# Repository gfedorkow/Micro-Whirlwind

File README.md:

Schematic and printed circuit KiCad design files for a hand-held Whirlwind emulator based on the Raspberry Pi

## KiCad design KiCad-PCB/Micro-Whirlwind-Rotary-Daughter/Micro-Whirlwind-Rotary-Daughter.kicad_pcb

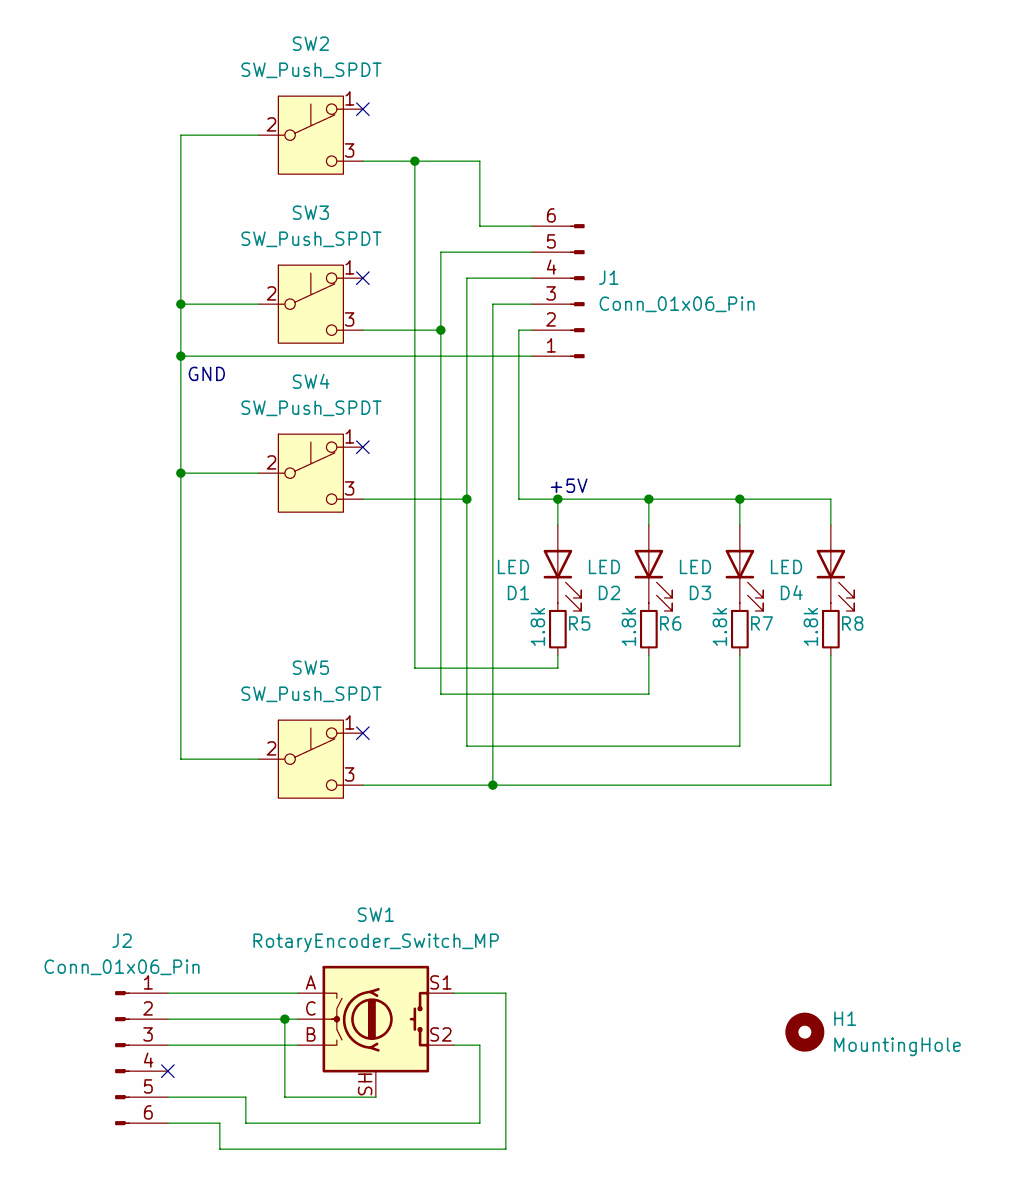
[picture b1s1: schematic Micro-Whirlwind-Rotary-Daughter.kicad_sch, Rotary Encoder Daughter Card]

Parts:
D1, D2, D3, D4: LED; LED_D3.0mm
H1: MountingHole; MountingHole_3.2mm_M3
J1, J2: Conn_01x06_Pin; PinHeader_1x06_P2.54mm_Vertical
R5, R6, R7, R8: 1.8k; R_1206_3216Metric_Pad1.30x1.75mm_HandSolder
SW1: RotaryEncoder_Switch_MP; RotaryEncoder_Bourns_Vertical_PEC12R-3x17F-Sxxxx
SW2, SW3, SW4, SW5: SW_Push_SPDT; PinHeader_1x03_P2.54mm_Vertical

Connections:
unnamed: D1.2 (A), D2.2 (A), D3.2 (A), D4.2 (A), J1.2
unnamed: D1.1 (K), R5.1
unnamed: D2.1 (K), R6.1
unnamed: D3.1 (K), R7.1
unnamed: D4.1 (K), R8.1
unnamed: J1.1, SW2.2 (B), SW3.2 (B), SW4.2 (B), SW5.2 (B)
unnamed: J1.3, R8.2, SW5.3 (C)
unnamed: J1.4, R7.2, SW4.3 (C)
unnamed: J1.5, R6.2, SW3.3 (C)
unnamed: J1.6, R5.2, SW2.3 (C)
unnamed: J2.1, SW1.A
unnamed: J2.2, SW1.C, SW1.SH
unnamed: J2.3, SW1.B
unnamed: J2.5, SW1.S2
unnamed: J2.6, SW1.S1

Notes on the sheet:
GND
+5V

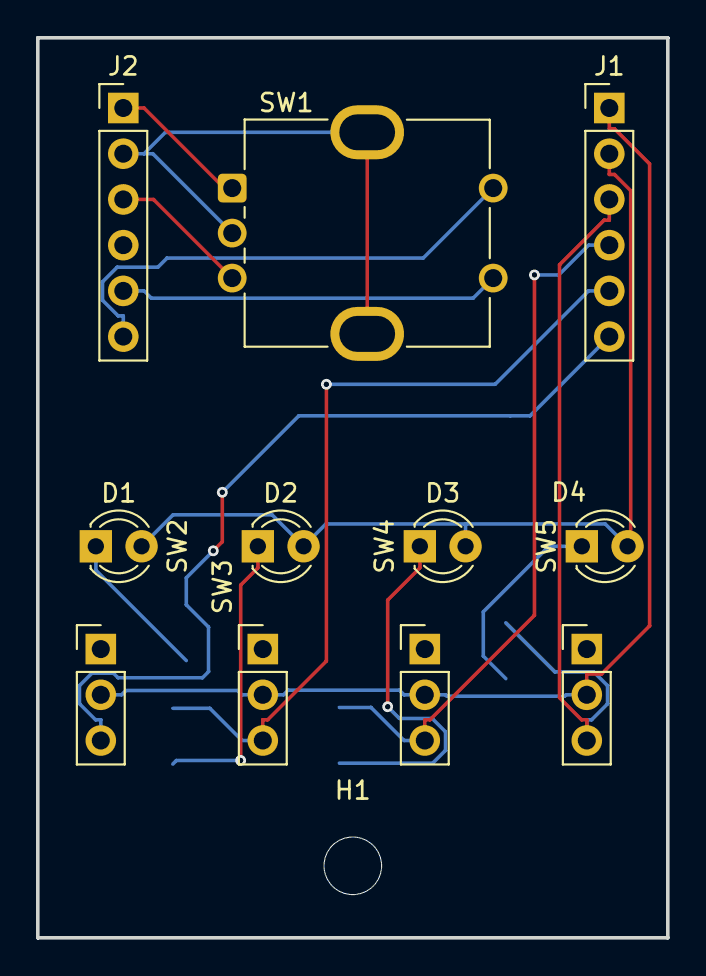
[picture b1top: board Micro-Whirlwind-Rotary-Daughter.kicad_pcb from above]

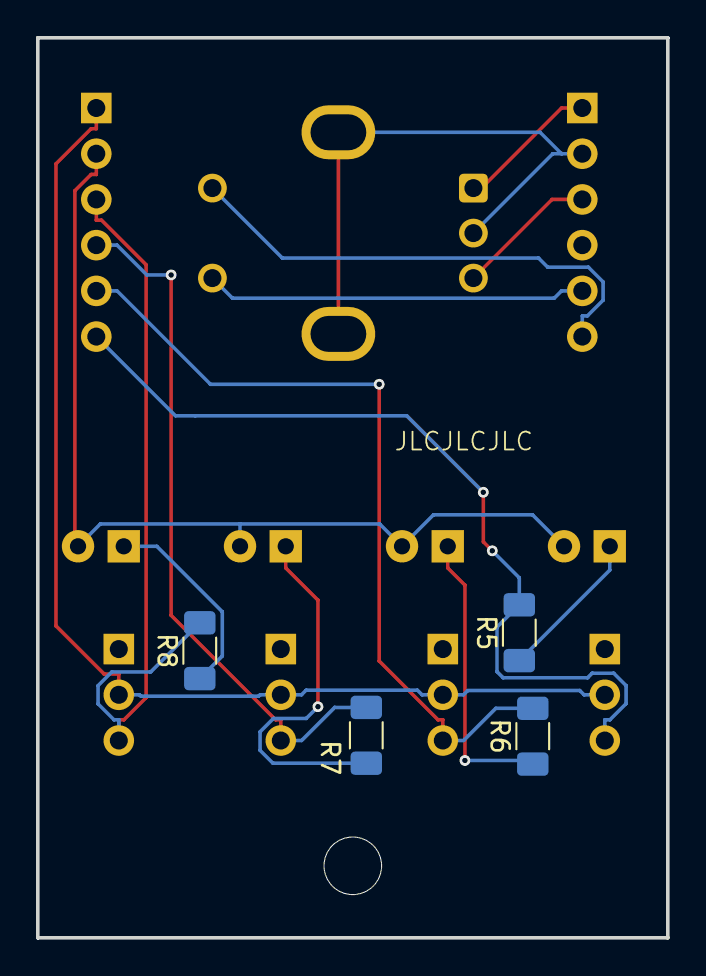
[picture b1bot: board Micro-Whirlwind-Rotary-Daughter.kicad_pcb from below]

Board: 2 copper layers, 35.0 x 50.0 mm, 16 parts (4 on the bottom side), 15 nets.

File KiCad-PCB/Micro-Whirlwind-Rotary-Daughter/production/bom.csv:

Designator,Footprint,Quantity,Value,LCSC Part #
"D1, D2, D3, D4",LED_D3.0mm,4,LED,
"J1, J2",PinHeader_1x06_P2.54mm_Vertical,2,Conn_01x06_Pin,
"R5, R6, R7, R8",1206,4,1.8k,
SW1,RotaryEncoder_Bourns_Vertical_PEC12R-3x17F-Sxxxx,1,RotaryEncoder_Switch_MP,
"SW2, SW3, SW4, SW5",PinHeader_1x03_P2.54mm_Vertical,4,SW_Push_SPDT,

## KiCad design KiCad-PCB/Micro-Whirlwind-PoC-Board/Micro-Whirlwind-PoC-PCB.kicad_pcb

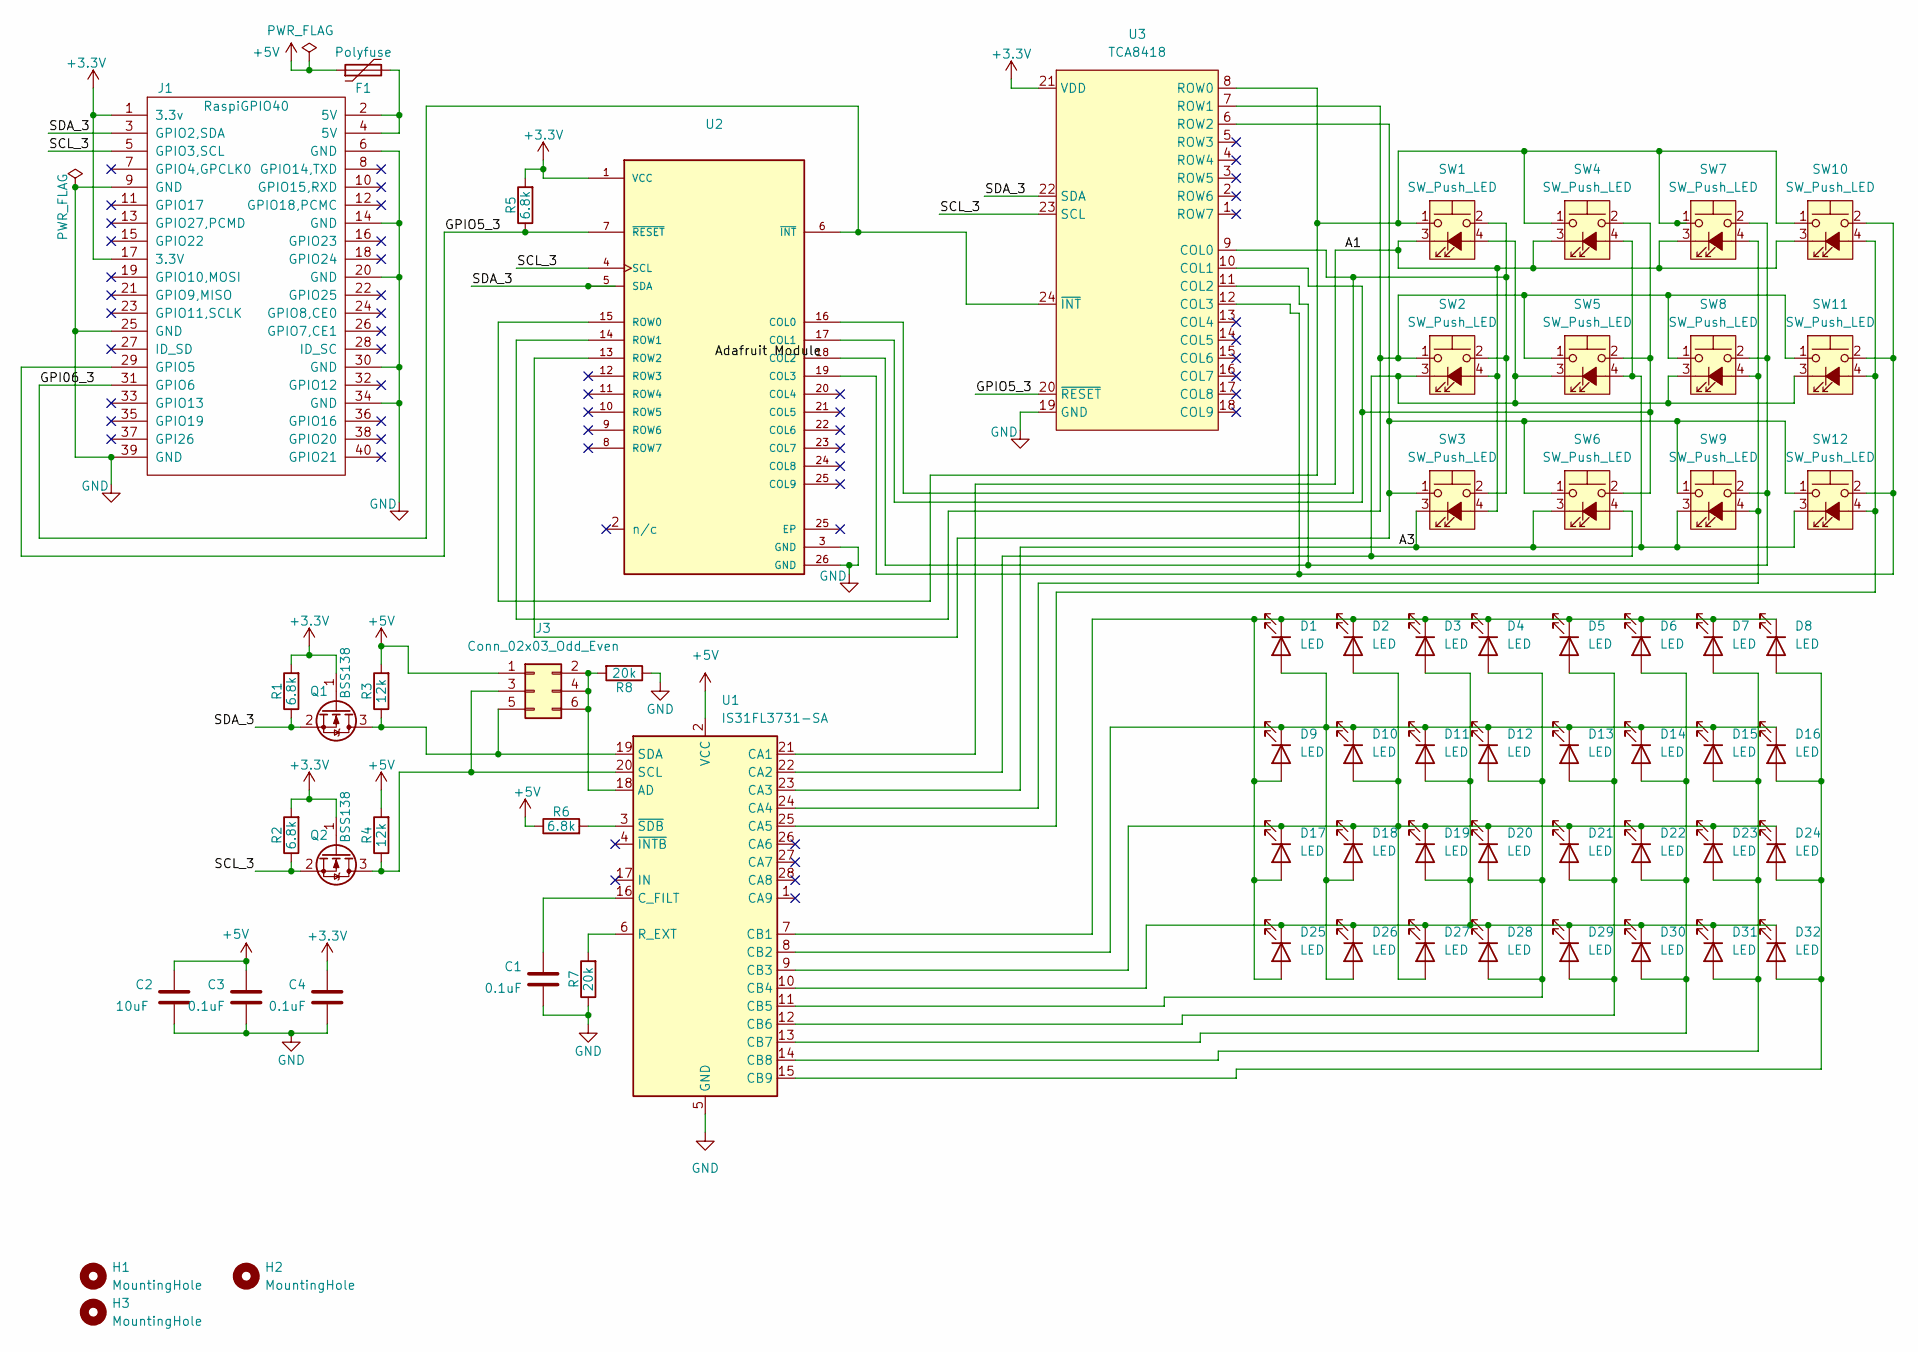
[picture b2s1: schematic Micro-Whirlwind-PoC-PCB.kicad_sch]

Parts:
C1, C3, C4: 0.1uF; C_Rect_L11.0mm_W2.8mm_P10.00mm_MKT
C2: 10uF; CP_Radial_D5.0mm_P2.50mm
D1, D2, D3, D4, D5, D6, D7, D8, D9, D10, D11, D12, D13, D14, D15, D16, D17, D18, D19, D20, D21, D22, D23, D24, D25, D26, D27, D28, D29, D30, D31, D32: LED; LED_D3.0mm
F1: Polyfuse; Fuse_Bourns_MF-RG300
H1, H2, H3: MountingHole; MountingHole_2.5mm_panel_cut
J1: RaspiGPIO40; Wannenstecker_2x20_V
J3: Conn_02x03_Odd_Even; PinHeader_2x03_P2.54mm_Vertical
Q1, Q2: BSS138; SOT-23
R1, R2, R5, R6: 6.8k; SM-1206B
R3, R4: 12k; SM-1206B
R7, R8: 20k; SM-1206B
SW1, SW2, SW3, SW4, SW5, SW6, SW7, SW8, SW9, SW10, SW11, SW12: SW_Push_LED; SW_PUSH_and_LED_6mm_H8mm
U1: IS31FL3731-SA; SSOP-28_5.3x10.2mm_P0.65mm
U2: TCA8418RTWR-Module; AdaFruit_2x13_header; PARTREV G
U3: TCA8418; WQFN-24-1EP_4x4mm_P0.5mm_EP2.45x2.45mm

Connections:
+3.3V: C4.1, J1.1 (3.3v), J1.17 (3.3V), Q1.1 (G), Q2.1 (G), R1.2, R2.2, R5.2, U2.1 (VCC), U3.21 (VDD)
+5V: C2.1, C3.1, F1.1, J3.1, R3.2, R4.2, R6.1, U1.2 (VCC)
/A1: SW1.3 (K), SW2.4 (A), SW3.4 (A), SW4.3 (K), SW7.3 (K), SW10.3 (K), U1.21 (CA1)
/A3: SW3.3 (K), SW4.4 (A), SW5.4 (A), SW6.3 (K), SW9.3 (K), SW12.3 (K), U1.23 (CA3)
/GPI06_3: J1.31 (GPIO6), U2.6 (~INT), U3.24 (~INT)
/GPIO5_3: J1.29 (GPIO5), R5.1, U2.7 (~RESET), U3.20 (~RESET)
/SCL_3: J1.5 (GPIO3,SCL), Q2.2 (S), R2.1, U2.4 (SCL), U3.23 (SCL)
/SDA_3: J1.3 (GPIO2,SDA), Q1.2 (S), R1.1, U2.5 (SDA), U3.22 (SDA)
GND: C1.2, C2.2, C3.2, C4.2, J1.6 (GND), J1.9 (GND), J1.14 (GND), J1.20 (GND), J1.25 (GND), J1.30 (GND), J1.34 (GND), J1.39 (GND), R7.1, R8.1, U1.5 (GND), U2.3 (GND), U2.26 (GND), U3.19 (GND)
unnamed: D1.2 (A), D9.1 (K), D10.1 (K), D11.1 (K), D12.1 (K), D13.1 (K), D14.1 (K), D15.1 (K), D16.1 (K), D18.2 (A), D26.2 (A), U1.8 (CB2)
unnamed: D1.1 (K), D2.1 (K), D3.1 (K), D4.1 (K), D5.1 (K), D6.1 (K), D7.1 (K), D8.1 (K), D9.2 (A), D17.2 (A), D25.2 (A), U1.7 (CB1)
unnamed: D2.2 (A), D10.2 (A), D17.1 (K), D18.1 (K), D19.1 (K), D20.1 (K), D21.1 (K), D22.1 (K), D23.1 (K), D24.1 (K), D27.2 (A), U1.9 (CB3)
unnamed: D3.2 (A), D11.2 (A), D19.2 (A), D25.1 (K), D26.1 (K), D27.1 (K), D28.1 (K), D29.1 (K), D30.1 (K), D31.1 (K), D32.1 (K), U1.10 (CB4)
unnamed: D4.2 (A), D12.2 (A), D20.2 (A), D28.2 (A), U1.11 (CB5)
unnamed: D5.2 (A), D13.2 (A), D21.2 (A), D29.2 (A), U1.12 (CB6)
unnamed: D6.2 (A), D14.2 (A), D22.2 (A), D30.2 (A), U1.13 (CB7)
unnamed: D7.2 (A), D15.2 (A), D23.2 (A), D31.2 (A), U1.14 (CB8)
unnamed: D8.2 (A), D16.2 (A), D24.2 (A), D32.2 (A), U1.15 (CB9)
unnamed: F1.2, J1.2 (5V), J1.4 (5V)
unnamed: J3.2, J3.4, J3.6, R8.2, U1.18 (AD)
unnamed: J3.3, Q2.3 (D), R4.1, U1.20 (SCL)
unnamed: J3.5, Q1.3 (D), R3.1, U1.19 (SDA)
unnamed: SW1.4 (A), SW2.3 (K), SW5.3 (K), SW6.4 (A), SW8.3 (K), SW11.3 (K), U1.22 (CA2)
unnamed: SW7.4 (A), SW8.4 (A), SW9.4 (A), U1.24 (CA4)
unnamed: SW10.4 (A), SW11.4 (A), SW12.4 (A), U1.25 (CA5)
unnamed: C1.1, U1.16 (C_FILT)
unnamed: R7.2, U1.6 (R_EXT)
unnamed: R6.2, U1.3 (~SDB)
unnamed: SW1.2, SW2.2, SW3.2, U2.16 (COL0), U3.9 (COL0)
unnamed: SW4.2, SW5.2, SW6.2, U2.17 (COL1), U3.10 (COL1)
unnamed: SW7.2, SW8.2, SW9.2, U2.18 (COL2), U3.11 (COL2)
unnamed: SW10.2, SW11.2, SW12.2, U2.19 (COL3), U3.12 (COL3)
unnamed: SW1.1, SW4.1, SW7.1, SW10.1, U2.15 (ROW0), U3.8 (ROW0)
unnamed: SW2.1, SW5.1, SW8.1, SW11.1, U2.14 (ROW1), U3.7 (ROW1)
unnamed: SW3.1, SW6.1, SW9.1, SW12.1, U2.13 (ROW2), U3.6 (ROW2)

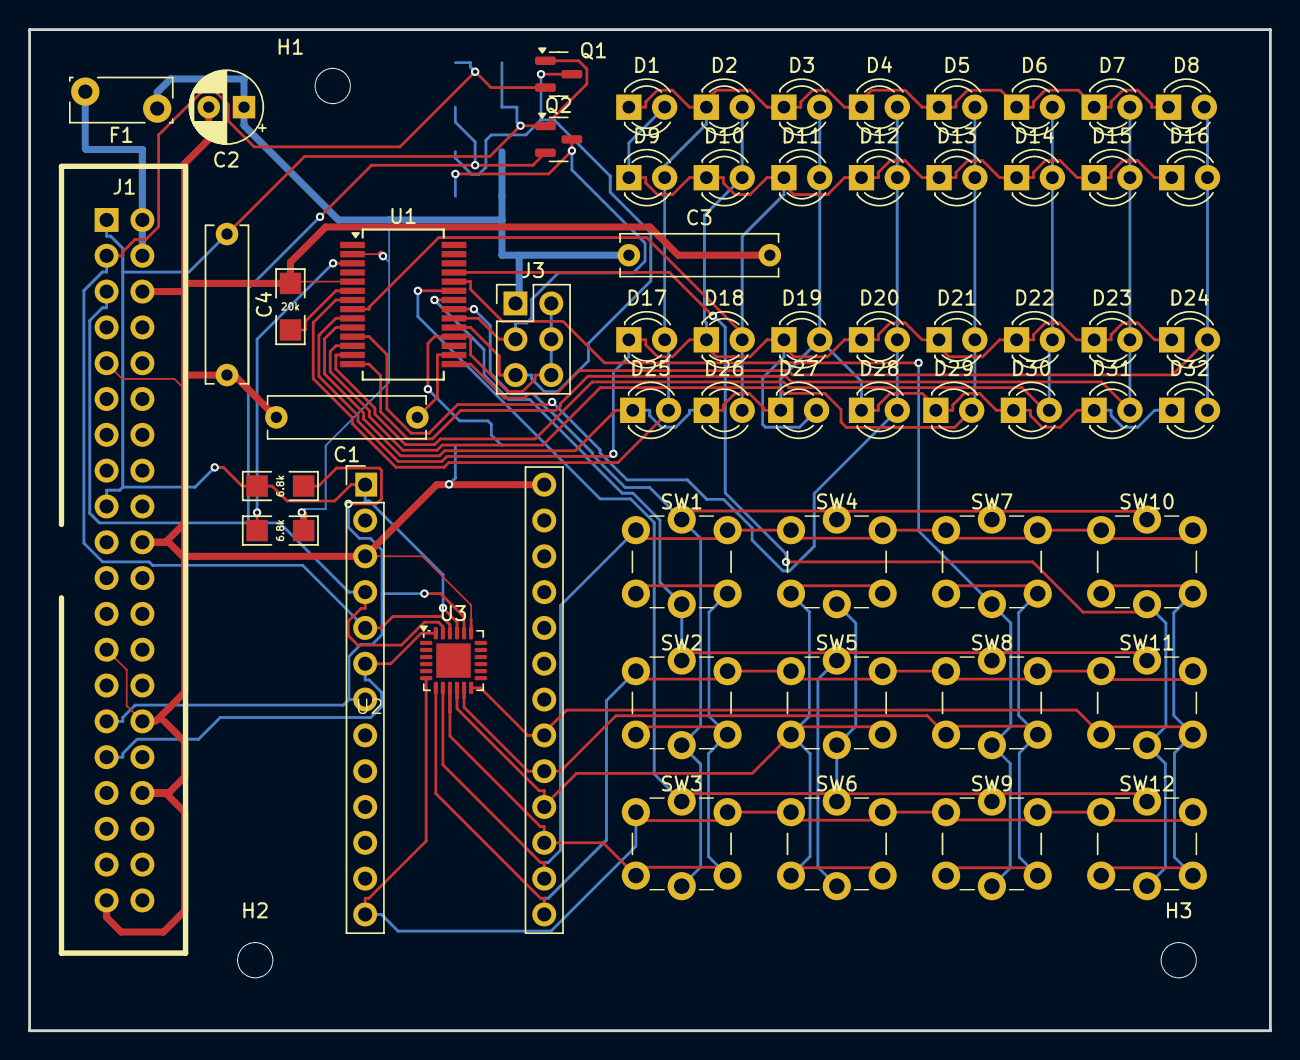
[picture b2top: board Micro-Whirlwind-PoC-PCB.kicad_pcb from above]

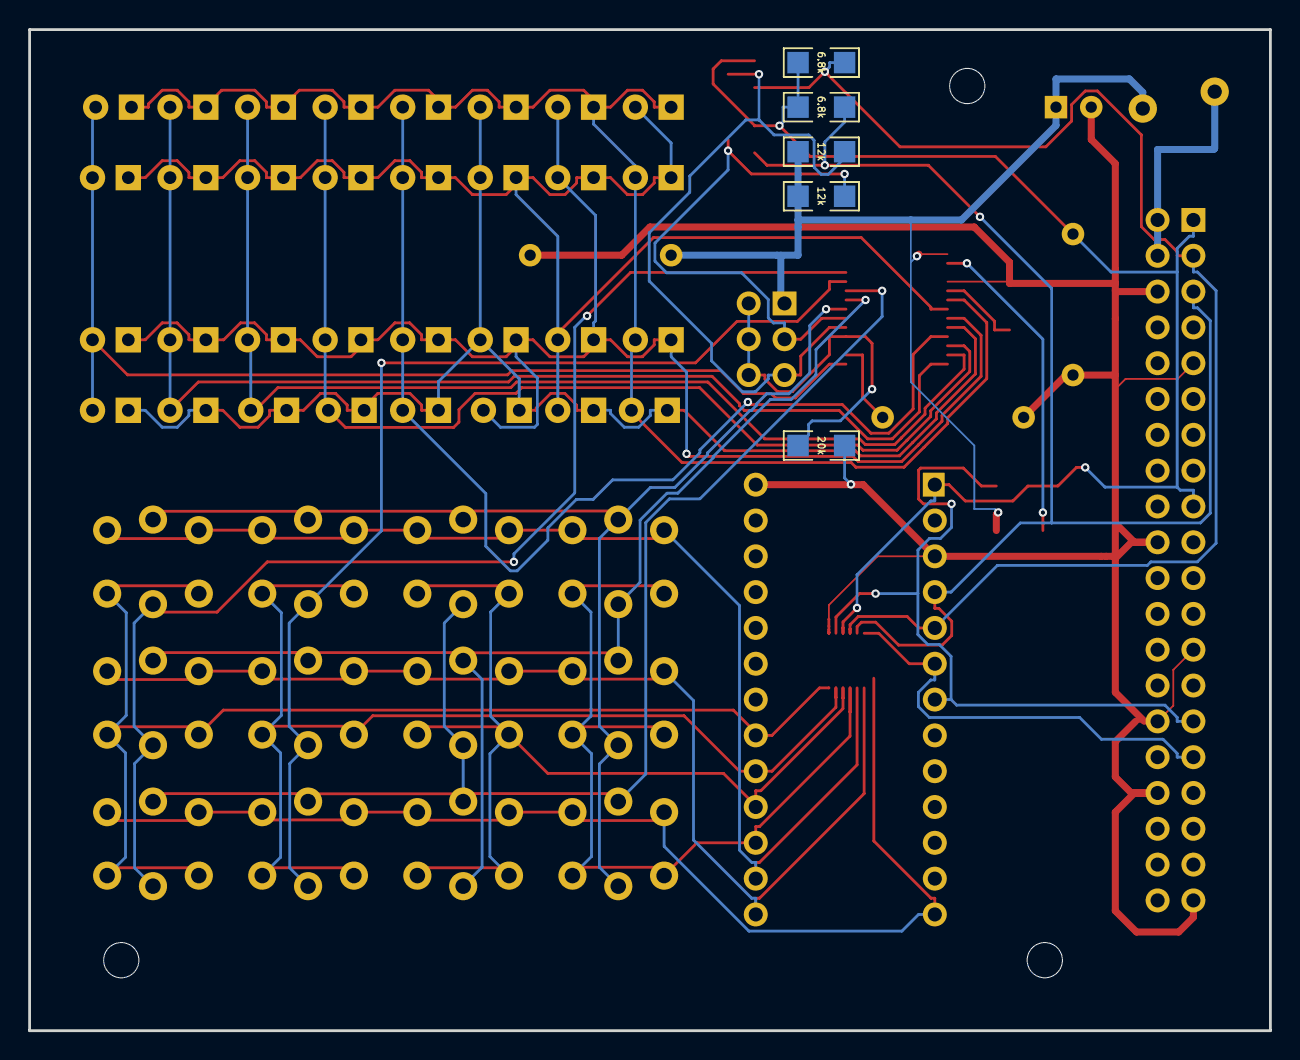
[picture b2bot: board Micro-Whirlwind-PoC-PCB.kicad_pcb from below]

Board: 2 copper layers, 88.0 x 71.0 mm, 67 parts (3 on the bottom side), 35 nets.

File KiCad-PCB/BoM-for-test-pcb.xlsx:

Designator | Footprint | Quantity | Value | LCSC Part #
C1, C3, C4 | C_Rect_L11.0mm_W2.8mm_P10.00mm_MKT | 3 | 0.1uF
C2 | CP_Radial_D5.0mm_P2.50mm | 1 | 10uF
D1, D10, D11, D12, D13, D14, D15, D16, D17, D18, D19, D2, D20, D21, D22, D23, D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 | LED_D3.0mm | 32 | LED
F1 | Fuse_Bourns_MF-RG300 | 1 | Polyfuse
J1 | Wannenstecker_2x20_V | 1 | RaspiGPIO40
J3 | PinHeader_2x03_P2.54mm_Vertical | 1 | Conn_02x03_Odd_Even
Q1, Q2 | SOT-23 | 2 | BSS138
R1, R2, R5, R6 | SM-1206B | 4 | 6.8k
R3, R4 | SM-1206B | 2 | 12k
R7, R8 | SM-1206B | 2 | 20k
SW1, SW10, SW11, SW12, SW2, SW3, SW4, SW5, SW6, SW7, SW8, SW9 | SW_PUSH_and_LED_6mm_H8mm | 12 | SW_Push_LED
U1 | SSOP-28_5.3x10.2mm_P0.65mm | 1 | IS31FL3731-SA
U2 | AdaFruit_2x13_header | 1 | TCA8418RTWR-Module
U3 | WQFN-24-1EP_4x4mm_P0.5mm_EP2.45x2.45mm | 1 | TCA8418

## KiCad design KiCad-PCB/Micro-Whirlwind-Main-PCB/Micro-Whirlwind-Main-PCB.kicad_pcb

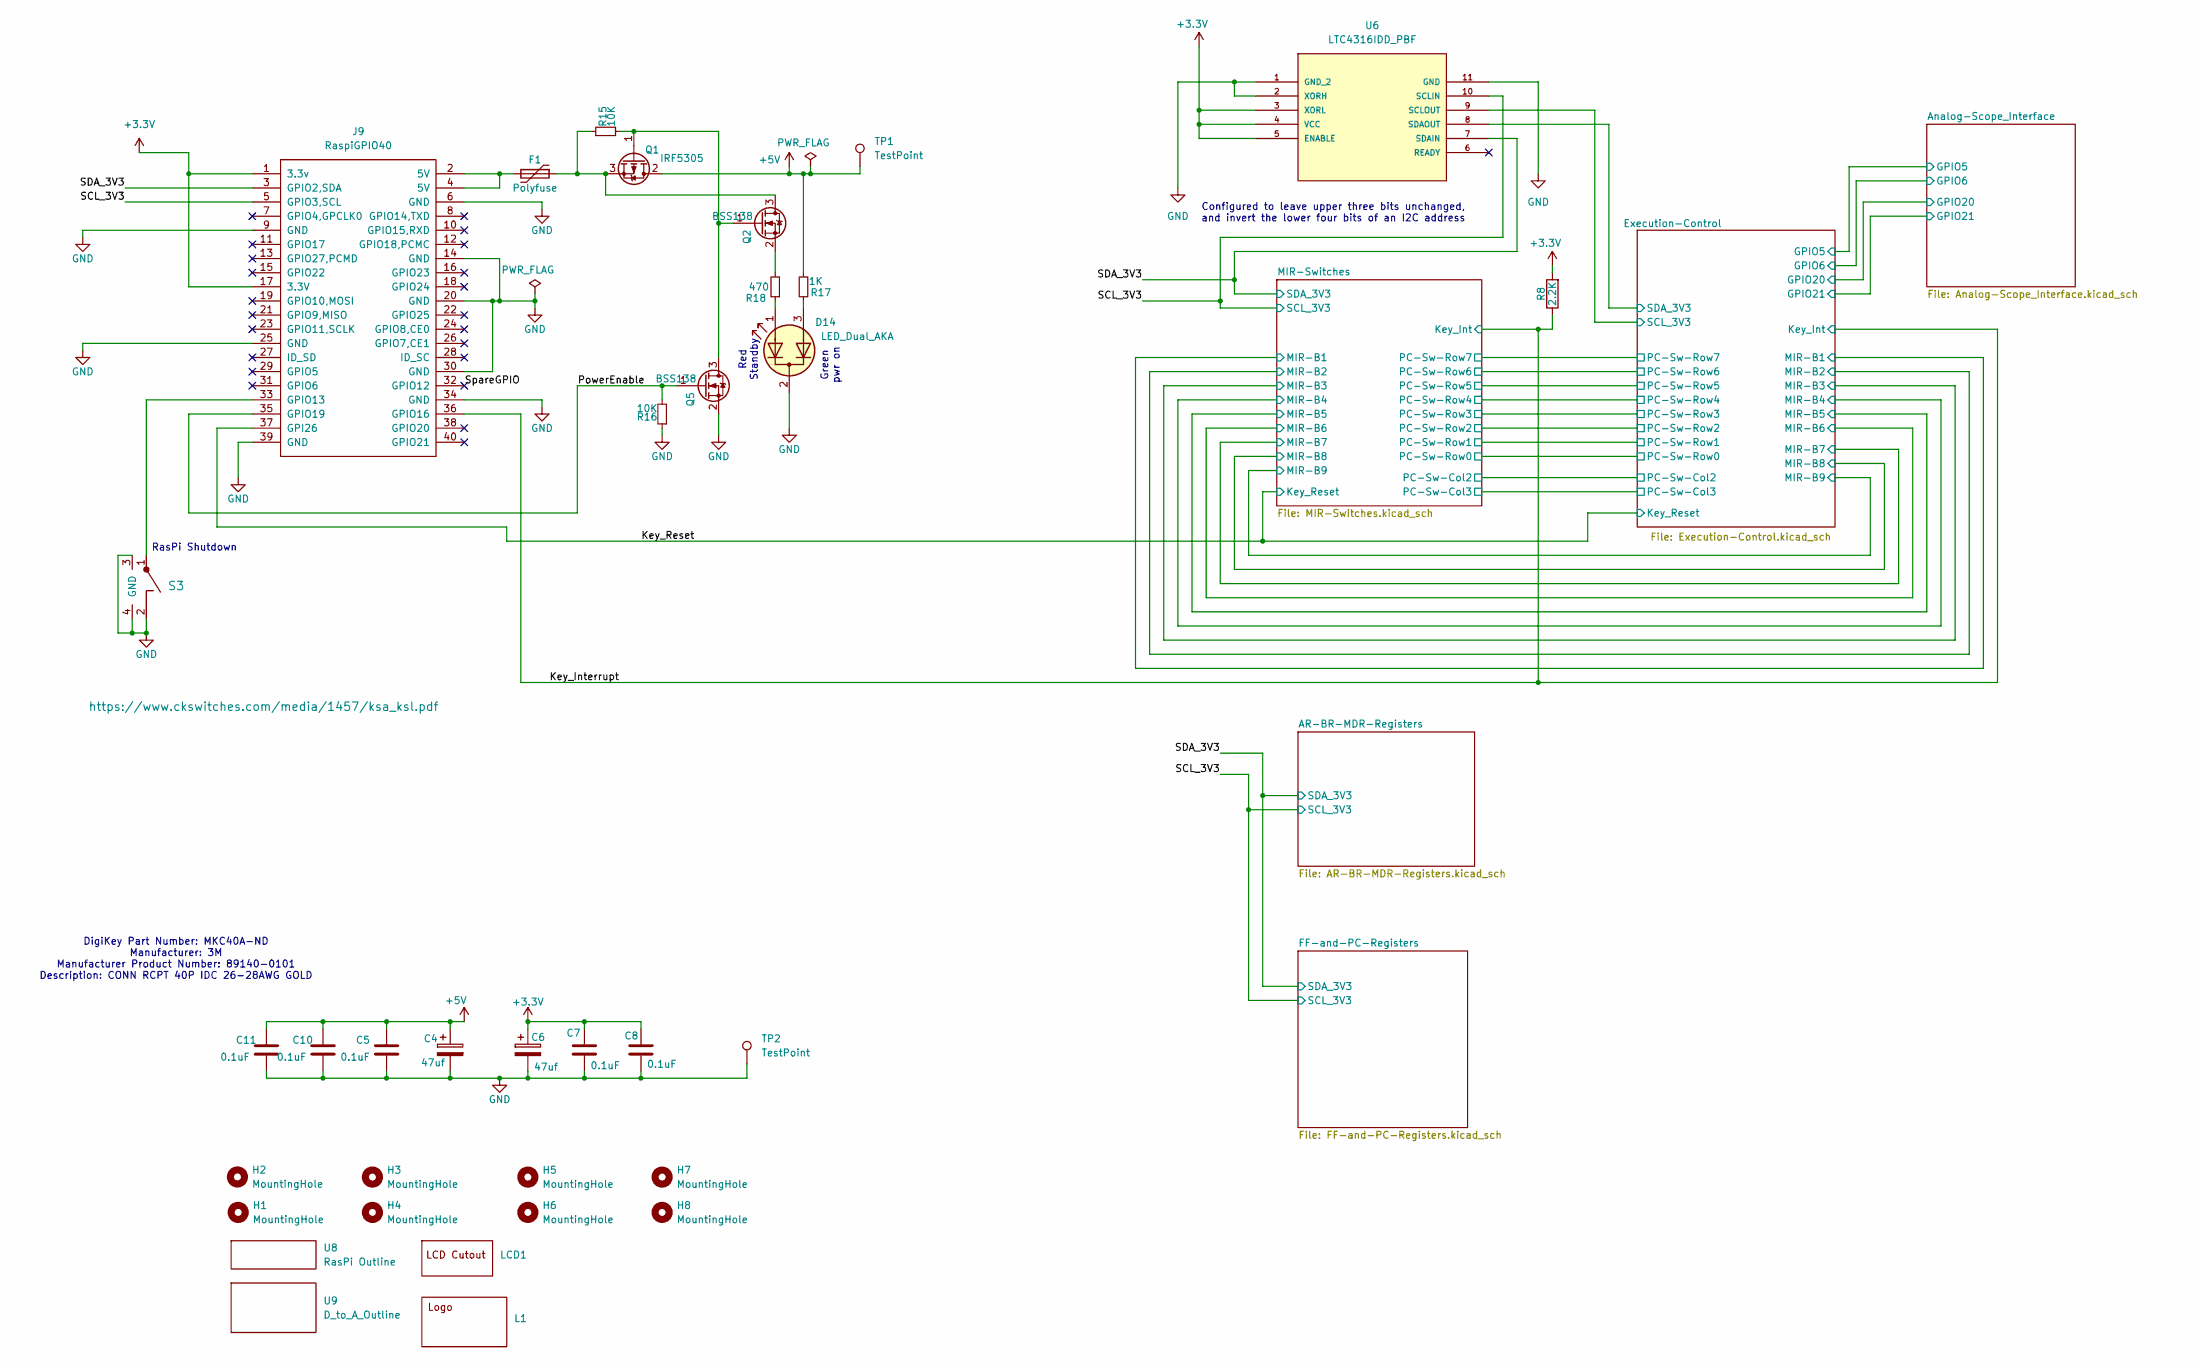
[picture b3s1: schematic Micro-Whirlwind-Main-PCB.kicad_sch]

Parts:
C4, C6: 47uf; CP_Radial_D5.0mm_P2.50mm
C5, C7, C8, C10, C11: 0.1uF; C_Rect_L7.0mm_W2.5mm_P5.00mm
D14: LED_Dual_AKA; LED_D3.0mm-3
F1: Polyfuse; Fuse_Bourns_MF-RG300
H1, H2, H3, H4, H5, H6, H7, H8: MountingHole; MountingHole_4_40_body
J9: RaspiGPIO40; PinHeader_2x20_P2.54mm_Vertical
L1: Logo-Large
LCD1: LCD-Cutout
Q1: IRF5305; TO-220-3_Horizontal_TabDown
Q2, Q5: BSS138; SOT-23
R8: 2.2K; SM-1206B
R15, R16: 10K; SM-1206B
R17: 1K; SM-1206B
R18: 470; SM-1206B
S3: RA_Push; SW_KSA0V311LFTR_CNK-RA-pushbutton
TP1, TP2: TestPoint; TestPoint_Loop_D2.50mm_Drill1.0mm
U6: LTC4316IDD_PBF; DFN-10_DD-with-clearance; MANUFACTURER_PART_NUMBER ltc4316idd#pbf
U8: RasPi Outline; RasPi-Outline
U9: D_to_A_Outline

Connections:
+3.3V: C6.1, C7.1, C8.1, J9.1 (3.3v), J9.17 (3.3V), R8.2, U6.3 (XORL), U6.4 (VCC), U6.5 (ENABLE); also elsewhere on the board
+5V: C4.1, C5.1, C10.1, C11.1, Q1.2 (D), R17.2, TP1.1; also elsewhere on the board
/Execution-Control/SCL_3V3: U6.9 (SCLOUT); also elsewhere on the board
/Execution-Control/SDA_3V3: U6.8 (SDAOUT); also elsewhere on the board
/Key_Interrupt: J9.36 (GPIO16), R8.1; also elsewhere on the board
/Key_Reset: J9.37 (GPI26); also elsewhere on the board
/PowerEnable: J9.35 (GPIO19), Q5.1 (G), R16.2
/SCL_3V3: J9.5 (GPIO3,SCL), U6.10 (SCLIN); also elsewhere on the board
/SDA_3V3: J9.3 (GPIO2,SDA), U6.7 (SDAIN); also elsewhere on the board
/SpareGPIO: J9.32 (GPIO12)
GND: C4.2, C5.2, C6.2, C7.2, C8.2, C10.2, C11.2, D14.2 (K), J9.6 (GND), J9.9 (GND), J9.14 (GND), J9.20 (GND), J9.25 (GND), J9.30 (GND), J9.34 (GND), J9.39 (GND), Q5.2 (S), R16.1, S3.2, S3.3 (GND), S3.4, TP2.1, U6.1 (GND_2), U6.2 (XORH), U6.11 (GND); also elsewhere on the board
unnamed: D14.1 (A1), R18.1
unnamed: D14.3 (A2), R17.1
unnamed: F1.2, J9.2 (5V), J9.4 (5V)
unnamed: J9.33 (GPIO13), S3.1
unnamed: Q1.1 (G), Q2.1 (G), Q5.3 (D), R15.2
unnamed: F1.1, Q1.3 (S), Q2.3 (D), R15.1
unnamed: Q2.2 (S), R18.2

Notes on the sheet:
Green pwr on
DigiKey Part Number: MKC40A-ND Manufacturer: 3M Manufacturer Product Number: 89140-0101 Description: CONN RCPT 40P IDC 26-28AWG GOLD
Configured to leave upper three bits unchanged, and invert the lower four bits of an I2C address
Red Standby
RasPi Shutdown

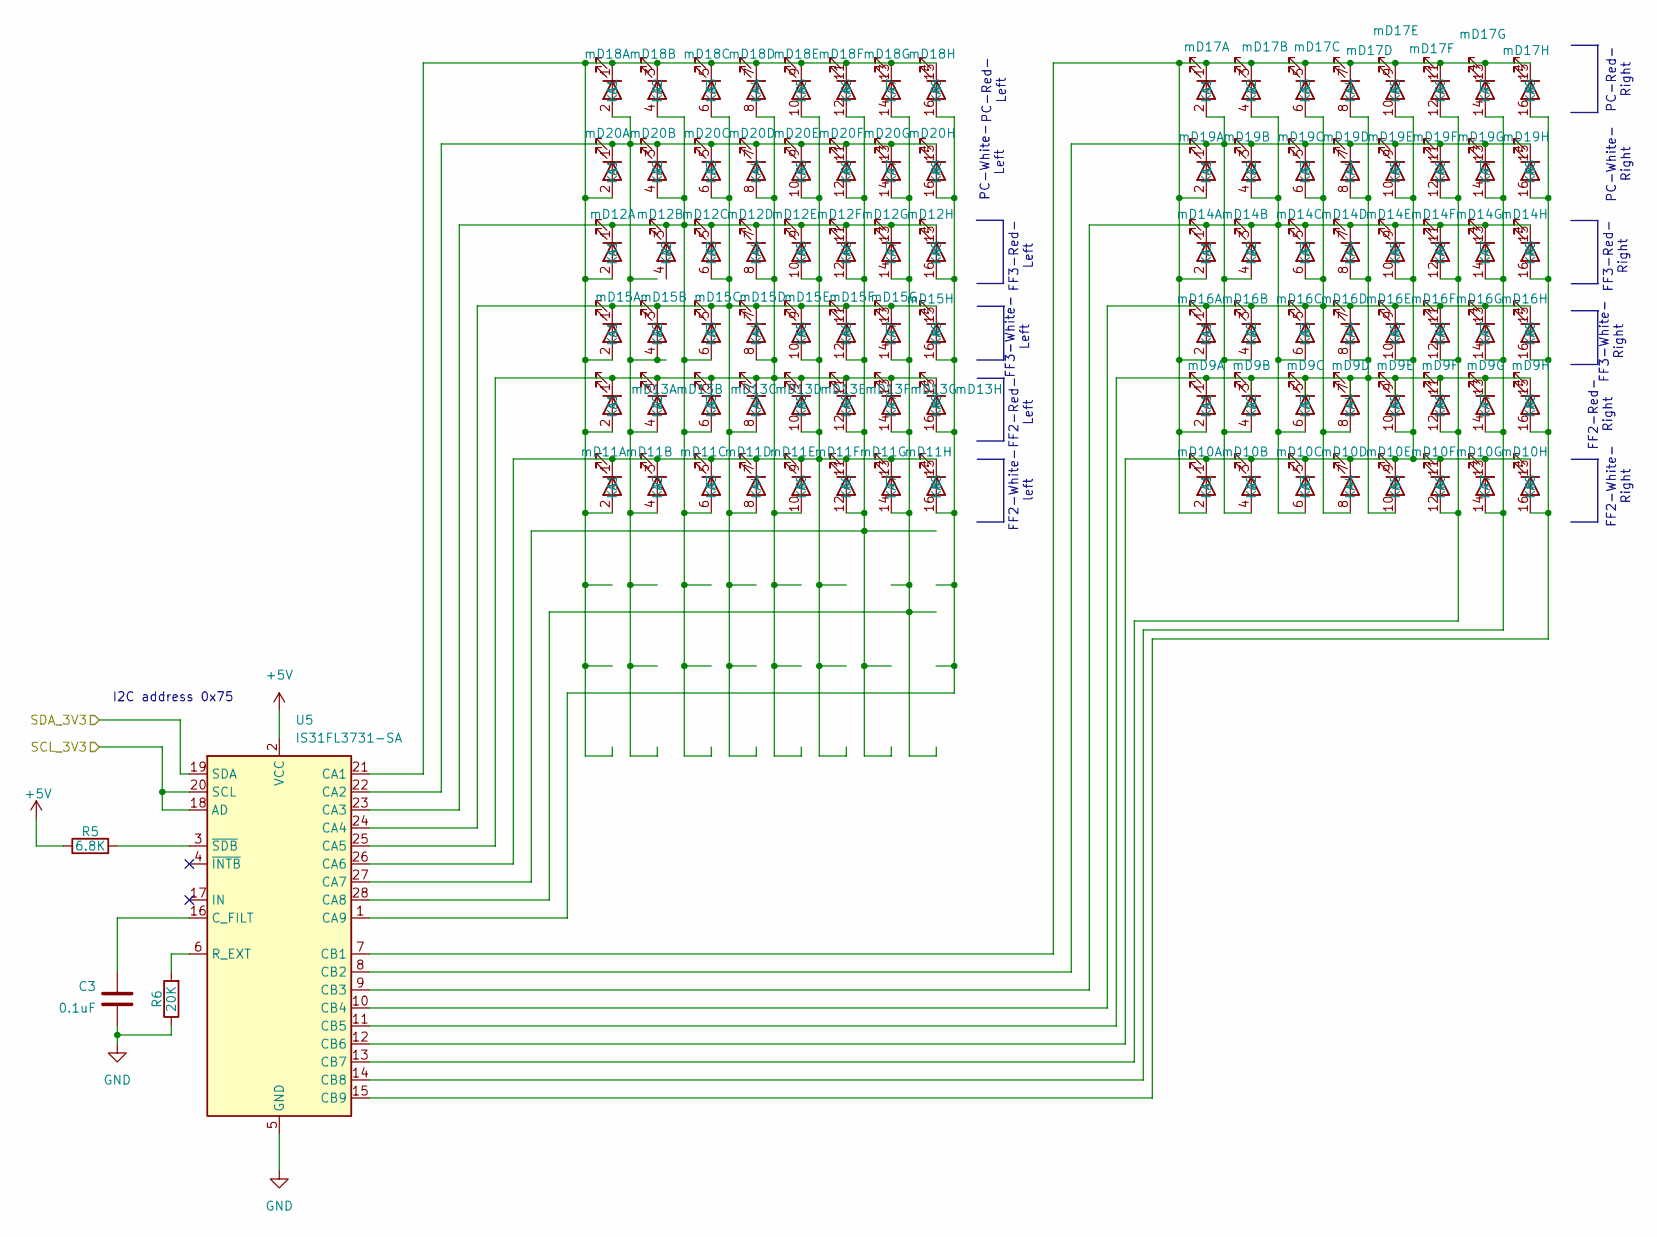
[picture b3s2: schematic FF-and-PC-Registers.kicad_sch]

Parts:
C3: 0.1uF; C_Rect_L7.0mm_W2.5mm_P5.00mm
R5: 6.8K; SM-1206B
R6: 20K; SM-1206B
U5: IS31FL3731-SA; SSOP-28_5.3x10.2mm_P0.65mm
mD9, mD10, mD11, mD12, mD13, mD14, mD15, mD16, mD17, mD18, mD19, mD20: LED_D3.0mm_8x_bank

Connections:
+5V: R5.1, U5.2 (VCC); also elsewhere on the board
/SCL_3V3: U5.18 (AD), U5.20 (SCL); also elsewhere on the board
/SDA_3V3: U5.19 (SDA); also elsewhere on the board
GND: C3.2, R6.1, U5.5 (GND); also elsewhere on the board
unnamed: U5.21 (CA1), mD11.2 (A1), mD12.2 (A1), mD13.2 (A1), mD15.2 (A1), mD18.1 (K1), mD18.3 (K2), mD18.5 (K3), mD18.7 (K4), mD18.9 (K5), mD18.11 (K6), mD18.13 (K7), mD18.15 (K8), mD20.2 (A1)
unnamed: U5.22 (CA2), mD11.4 (A2), mD13.4 (A2), mD15.4 (A2), mD18.2 (A1), mD20.1 (K1), mD20.3 (K2), mD20.5 (K3), mD20.7 (K4), mD20.9 (K5), mD20.11 (K6), mD20.13 (K7), mD20.15 (K8)
unnamed: U5.23 (CA3), mD11.6 (A3), mD12.1 (K1), mD12.3 (K2), mD12.5 (K3), mD12.7 (K4), mD12.9 (K5), mD12.11 (K6), mD12.13 (K7), mD12.15 (K8), mD13.6 (A3), mD15.6 (A3), mD18.4 (A2), mD20.4 (A2)
unnamed: U5.24 (CA4), mD11.8 (A4), mD12.6 (A3), mD13.8 (A4), mD15.1 (K1), mD15.3 (K2), mD15.5 (K3), mD15.7 (K4), mD15.9 (K5), mD15.11 (K6), mD15.13 (K7), mD15.15 (K8), mD18.6 (A3), mD20.6 (A3)
unnamed: U5.25 (CA5), mD11.10 (A5), mD12.8 (A4), mD13.1 (K1), mD13.3 (K2), mD13.5 (K3), mD13.7 (K4), mD13.9 (K5), mD13.11 (K6), mD13.13 (K7), mD13.15 (K8), mD15.8 (A4), mD18.8 (A4), mD20.8 (A4)
unnamed: U5.26 (CA6), mD11.1 (K1), mD11.3 (K2), mD11.5 (K3), mD11.7 (K4), mD11.9 (K5), mD11.11 (K6), mD11.13 (K7), mD11.15 (K8), mD12.10 (A5), mD13.10 (A5), mD15.10 (A5), mD18.10 (A5), mD20.10 (A5)
unnamed: U5.27 (CA7), mD11.12 (A6), mD12.12 (A6), mD13.12 (A6), mD15.12 (A6), mD18.12 (A6), mD20.12 (A6)
unnamed: U5.28 (CA8), mD11.14 (A7), mD12.14 (A7), mD13.14 (A7), mD15.14 (A7), mD18.14 (A7), mD20.14 (A7)
unnamed: U5.1 (CA9), mD11.16 (A8), mD12.16 (A8), mD13.16 (A8), mD15.16 (A8), mD18.16 (A8), mD20.16 (A8)
unnamed: U5.7 (CB1), mD9.2 (A1), mD10.2 (A1), mD14.2 (A1), mD16.2 (A1), mD17.1 (K1), mD17.3 (K2), mD17.5 (K3), mD17.7 (K4), mD17.9 (K5), mD17.11 (K6), mD17.13 (K7), mD17.15 (K8), mD19.2 (A1)
unnamed: U5.8 (CB2), mD9.4 (A2), mD10.4 (A2), mD14.4 (A2), mD16.4 (A2), mD17.2 (A1), mD19.1 (K1), mD19.3 (K2), mD19.5 (K3), mD19.7 (K4), mD19.9 (K5), mD19.11 (K6), mD19.13 (K7), mD19.15 (K8)
unnamed: U5.9 (CB3), mD9.6 (A3), mD10.6 (A3), mD14.1 (K1), mD14.3 (K2), mD14.5 (K3), mD14.7 (K4), mD14.9 (K5), mD14.11 (K6), mD14.13 (K7), mD14.15 (K8), mD16.6 (A3), mD17.4 (A2), mD19.4 (A2)
unnamed: U5.10 (CB4), mD9.8 (A4), mD10.8 (A4), mD14.6 (A3), mD16.1 (K1), mD16.3 (K2), mD16.5 (K3), mD16.7 (K4), mD16.9 (K5), mD16.11 (K6), mD16.13 (K7), mD16.15 (K8), mD17.6 (A3), mD19.6 (A3)
unnamed: U5.11 (CB5), mD9.1 (K1), mD9.3 (K2), mD9.5 (K3), mD9.7 (K4), mD9.9 (K5), mD9.11 (K6), mD9.13 (K7), mD9.15 (K8), mD10.10 (A5), mD14.8 (A4), mD16.8 (A4), mD17.8 (A4), mD19.8 (A4)
unnamed: U5.12 (CB6), mD9.10 (A5), mD10.1 (K1), mD10.3 (K2), mD10.5 (K3), mD10.7 (K4), mD10.9 (K5), mD10.11 (K6), mD10.13 (K7), mD10.15 (K8), mD14.10 (A5), mD16.10 (A5), mD17.10 (A5), mD19.10 (A5)
unnamed: U5.13 (CB7), mD9.12 (A6), mD10.12 (A6), mD14.12 (A6), mD16.12 (A6), mD17.12 (A6), mD19.12 (A6)
unnamed: U5.14 (CB8), mD9.14 (A7), mD10.14 (A7), mD14.14 (A7), mD16.14 (A7), mD17.14 (A7), mD19.14 (A7)
unnamed: U5.15 (CB9), mD9.16 (A8), mD10.16 (A8), mD14.16 (A8), mD16.16 (A8), mD17.16 (A8), mD19.16 (A8)
unnamed: C3.1, U5.16 (C_FILT)
unnamed: R6.2, U5.6 (R_EXT)
unnamed: R5.2, U5.3 (~SDB)

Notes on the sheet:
FF2-White- left
PC-White- Left
FF3-White- Right
I2C address 0x75
FF2-White- Right
PC-Red- Right
PC-White- Right
FF2-Red- Right
PC-Red- Left
FF3-Red- Left
FF3-Red- Right
FF2-Red- Left
FF3-White- Left

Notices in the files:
KiCad-PCB/Micro-Whirlwind-Main-PCB/Micro-Whirlwind-Main-PCB.kicad_pcb:
Copyright 2024
